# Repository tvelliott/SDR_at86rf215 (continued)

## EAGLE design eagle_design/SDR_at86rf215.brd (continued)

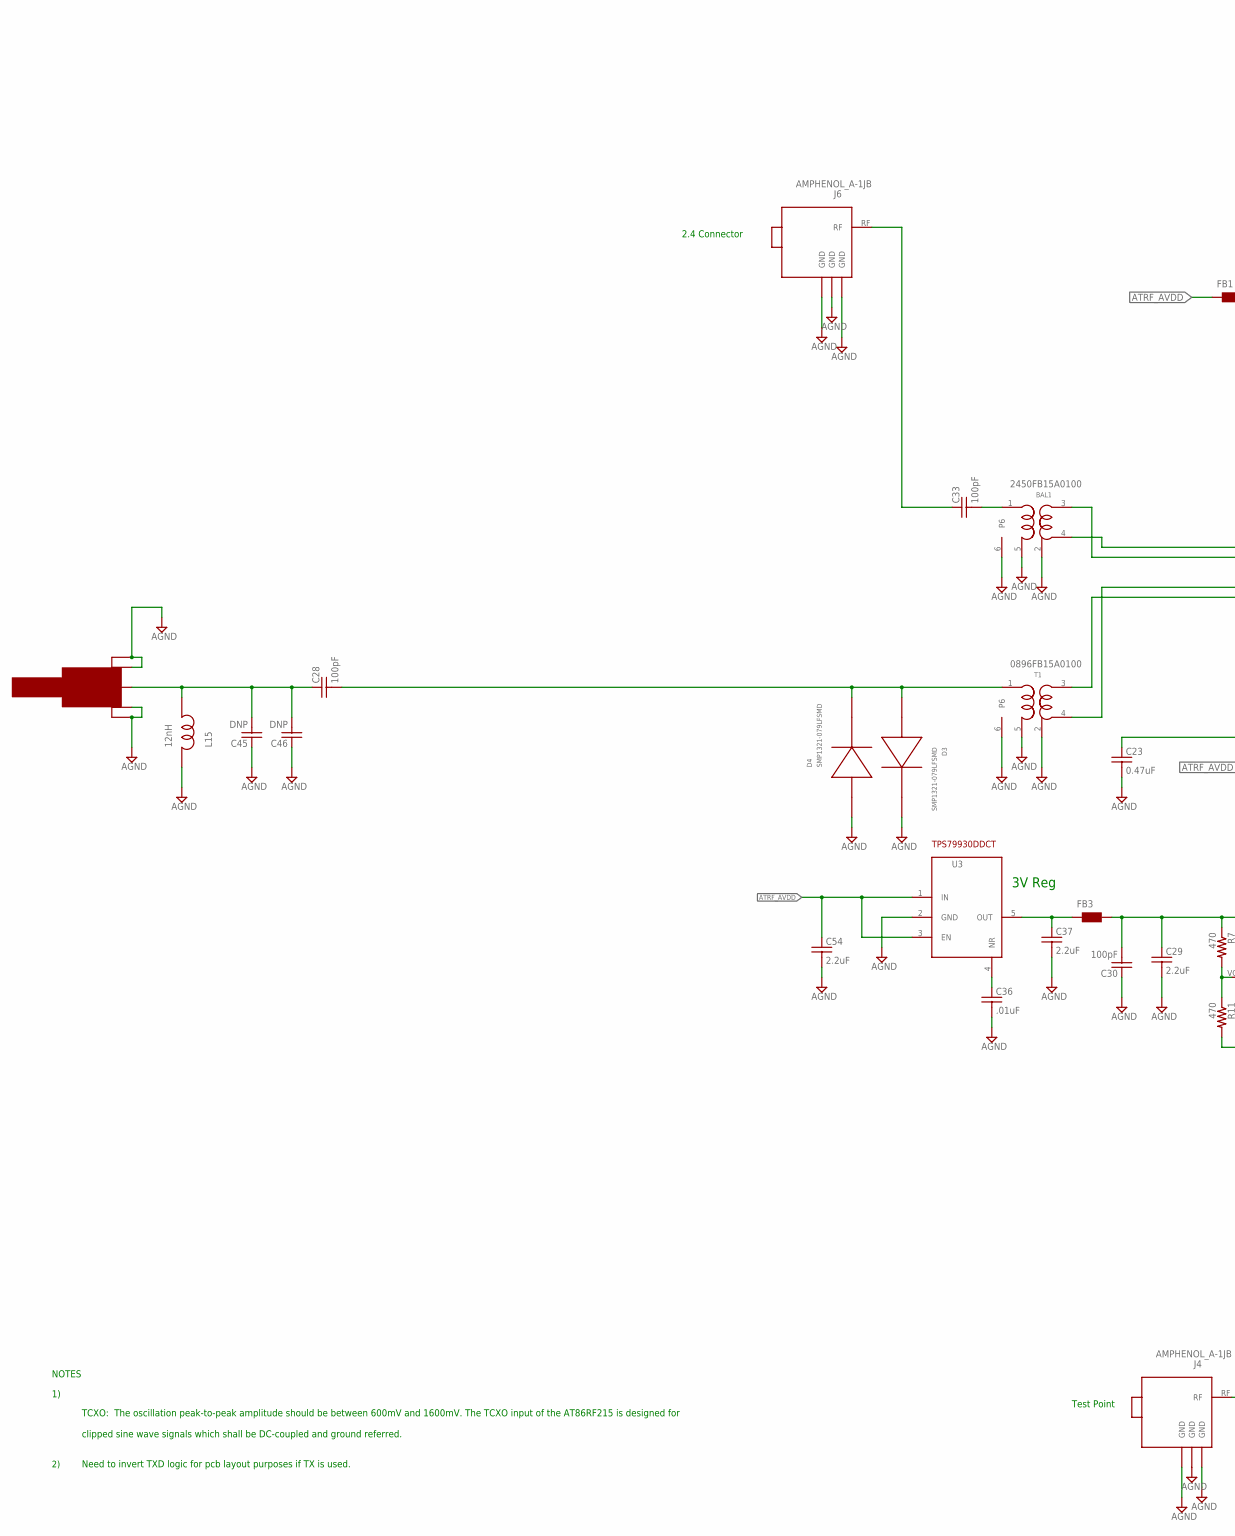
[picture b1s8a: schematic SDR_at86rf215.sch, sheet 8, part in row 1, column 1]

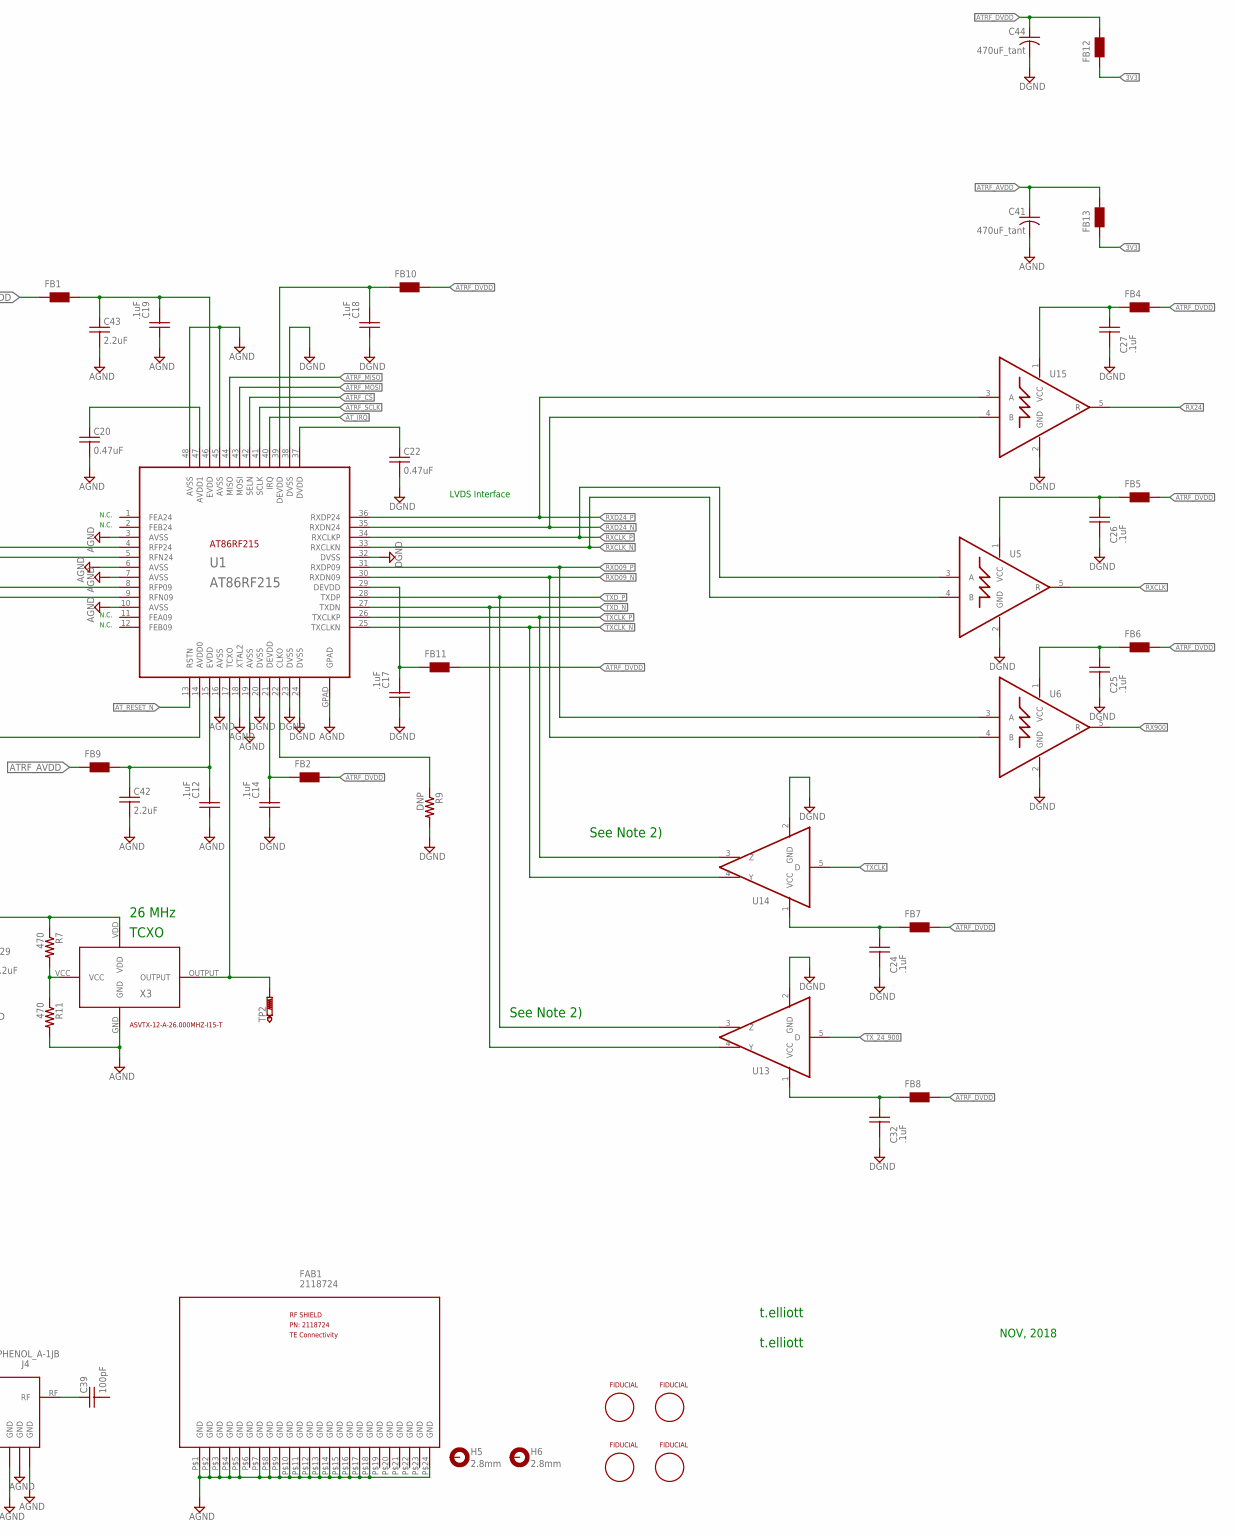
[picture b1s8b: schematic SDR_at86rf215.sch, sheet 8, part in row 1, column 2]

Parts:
BAL1: 2450FB15A0100; BALUN
C12, C14, C17, C18, C19, C24, C25, C26, C27, C32: .1uF; C0402
C20, C22, C23: 0.47uF; C0603
C28, C30, C33, C39: 100pF; C0603
C29, C37, C42, C43, C54: 2.2uF; C0603
C36: .01uF; C0603
C41, C44: 470uF_tant; 1210K
C45, C46: DNP; C0603
D3, D4: SMP1321-079LFSMD; SC-79_PINDIODE
FAB1: 2118724; RF_SHIELD
FB1, FB2, FB3, FB4, FB5, FB6, FB7, FB8, FB9, FB10, FB11, FB12, FB13: WE-CBF_0603; 0603
FID5, FID6, FID7, FID8: FIDUCIALSMD; FIDUCIAL
H5, H6: 2.8mm; 2,8-PAD
J3: SMA0.062; SMA_EDGE
J4, J6: AMPHENOL_A-1JB; UFLCONNECTOR
L15: 12nH; C0603
R7, R11: 470; R0603_COMPACT
R9: DNP; R0603_COMPACT
T1: 0896FB15A0100; BALUN
TP2: PTR1TP08R; TP08R
U1: AT86RF215; QFN48
U3: TPS799X; SOT23-6
U5, U6, U15: SN65LVDT2; SOT23-5
U13, U14: SN65LVDS1; SOT23-5
X3: ASVTX-12-A-40.000MHZ-H10-T; CRYSTAL_2.5_2MM

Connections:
3V: C29.1, C30.2, FB3.2, R7.1, X3.VDD
3V3: FB12.1, FB13.1; also elsewhere on the board
ATRF_AVDD: C41.A, C54.1, FB1.1, FB9.1, FB13.2, U3.1 (IN), U3.3 (EN)
ATRF_CS: U1.42 (SELN); also elsewhere on the board
ATRF_DVDD: C44.A, FB2.2, FB4.2, FB5.2, FB6.2, FB7.2, FB8.2, FB10.2, FB11.2, FB12.2
ATRF_MISO: U1.44 (MISO); also elsewhere on the board
ATRF_MOSI: U1.43 (MOSI); also elsewhere on the board
ATRF_SCLK: U1.41 (SCLK); also elsewhere on the board
AT_IRQ: U1.40 (IRQ); also elsewhere on the board
AT_RESET_N: U1.13 (RSTN); also elsewhere on the board
GND: BAL1.2 (FEED), BAL1.5 (GND), BAL1.6, C12.1, C14.1, C17.1, C18.1, C19.1, C20.2, C22.2, C23.2, C24.2, C25.2, C26.2, C27.2, C29.2, C30.1, C32.2, C36.2, C37.2, C41.C, C42.2, C43.2, C44.C, C45.1, C46.1, C54.2, D3.C, D4.A, FAB1.P$1, FAB1.P$2, FAB1.P$3, FAB1.P$4, FAB1.P$5, FAB1.P$7, FAB1.P$8, FAB1.P$9, FAB1.P$10, FAB1.P$11, FAB1.P$12, FAB1.P$13, FAB1.P$14, FAB1.P$15, FAB1.P$16, FAB1.P$17, FAB1.P$18, FAB1.P$24, J3.GND1, J3.GND2 (GND3), J3.GND3 (GND2), J3.GND4, J4.1 (GND), J4.2 (GND), J4.3 (GND), J6.1 (GND), J6.2 (GND), J6.3 (GND), L15.2, R9.2, R11.2, T1.2 (FEED), T1.5 (GND), T1.6, U1.3 (AVSS), U1.6 (AVSS), U1.7 (AVSS), U1.10 (AVSS), U1.16 (AVSS), U1.18 (XTAL2), U1.19 (AVSS), U1.20 (DVSS), U1.23 (DVSS), U1.24 (DVSS), U1.32 (DVSS), U1.38 (DVSS), U1.45 (AVSS), U1.48 (AVSS), U1.GPAD, U3.2 (GND), U5.2 (GND), U6.2 (GND), U13.2 (GND), U14.2 (GND), U15.2 (GND), X3.GND; also elsewhere on the board
unnamed: C36.1, U3.4 (NR)
unnamed: TP2.TP, U1.17 (TCXO), X3.OUTPUT
unnamed: C26.1, FB5.1, U5.1 (VCC)
unnamed: C20.1, U1.47 (AVDD1)
unnamed: C22.1, U1.37 (DVDD)
unnamed: C28.1, C45.2, C46.2, J3.RF, L15.1
unnamed: R7.2, R11.1, X3.VCC
unnamed: C27.1, FB4.1, U15.1 (VCC)
unnamed: C23.1, U1.14 (AVDD0)
unnamed: C39.1, J4.RF
unnamed: C32.1, FB8.1, U13.1 (VCC)
unnamed: R9.1, U1.22 (CLKO)
unnamed: BAL1.1 (UBAL), C33.2
unnamed: C12.2, C42.1, FB9.2, U1.15 (EVDD)
unnamed: C33.1, J6.RF
unnamed: C24.1, FB7.1, U14.1 (VCC)
unnamed: C25.1, FB6.1, U6.1 (VCC)
unnamed: C19.2, C43.1, FB1.2, U1.46 (EVDD)
unnamed: C14.2, FB2.1, U1.21 (DEVDD)
unnamed: C18.2, FB10.1, U1.39 (DEVDD)
unnamed: C17.2, FB11.1, U1.29 (DEVDD)
unnamed: C28.2, D3.A, D4.C, T1.1 (UBAL)
unnamed: C37.1, FB3.1, U3.5 (OUT)
RF09_N: T1.3 (BP2), U1.9 (RFN09)
RF09_P: T1.4 (BP1), U1.8 (RFP09)
RF24_N: BAL1.3 (BP2), U1.5 (RFN24)
RF24_P: BAL1.4 (BP1), U1.4 (RFP24)
RX24: U15.5 (R); also elsewhere on the board
RX900: U6.5 (R); also elsewhere on the board
RXCLK: U5.5 (R); also elsewhere on the board
RXCLK_N: U1.33 (RXCLKN), U5.4 (B)
RXCLK_P: U1.34 (RXCLKP), U5.3 (A)
RXD09_N: U1.30 (RXDN09), U6.4 (B)
RXD09_P: U1.31 (RXDP09), U6.3 (A)
RXD24_N: U1.35 (RXDN24), U15.4 (B)
RXD24_P: U1.36 (RXDP24), U15.3 (A)
TXCLK: U14.5 (D); also elsewhere on the board
TXCLK_N: U1.25 (TXCLKN), U14.4 (Y)
TXCLK_P: U1.26 (TXCLKP), U14.3 (Z)
TXD_N: U1.27 (TXDN), U13.4 (Y)
TXD_P: U1.28 (TXDP), U13.3 (Z)
TX_24_900: U13.5 (D); also elsewhere on the board

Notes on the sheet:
t.elliott
TCXO: The oscillation peak-to-peak amplitude should be between 600mV and 1600mV. The TCXO input of the AT86RF215 is designed for clipped sine wave signals which shall be DC-coupled and ground referred.
NOTES
TCXO
26 MHz
3V Reg
ASVTX-12-A-26.000MHZ-I15-T
LVDS Interface
See Note 2)
Need to invert TXD logic for pcb layout purposes if TX is used.
2.4 Connector
Test Point
N.C.
NOV, 2018

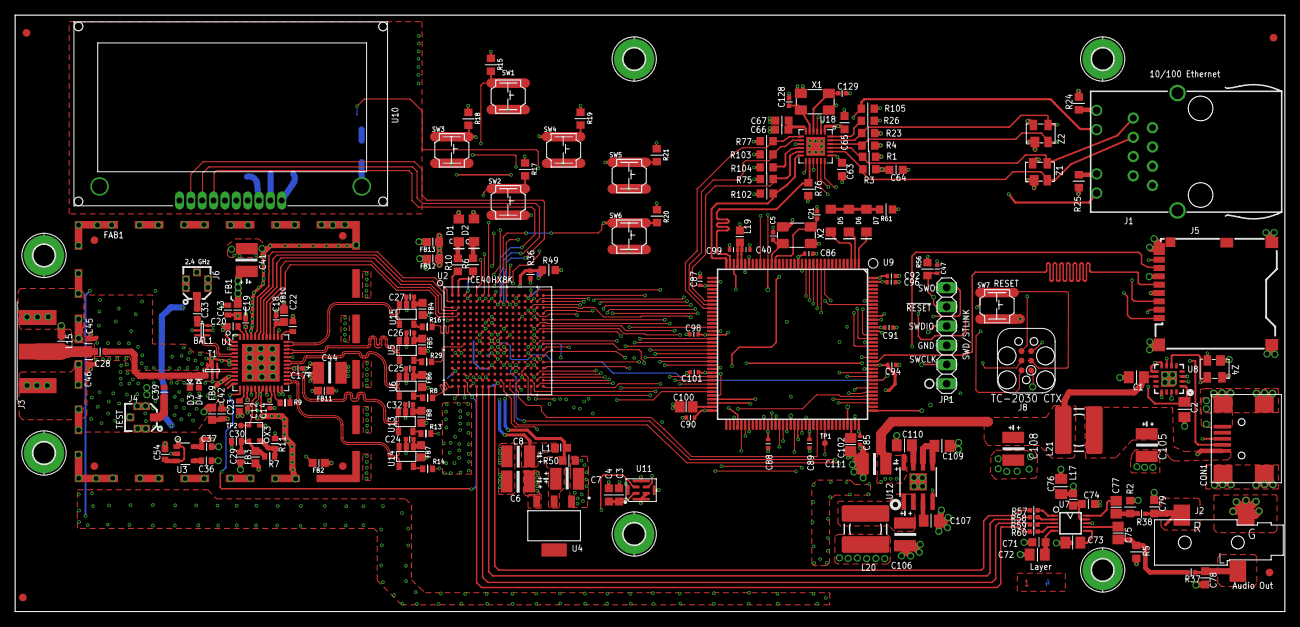
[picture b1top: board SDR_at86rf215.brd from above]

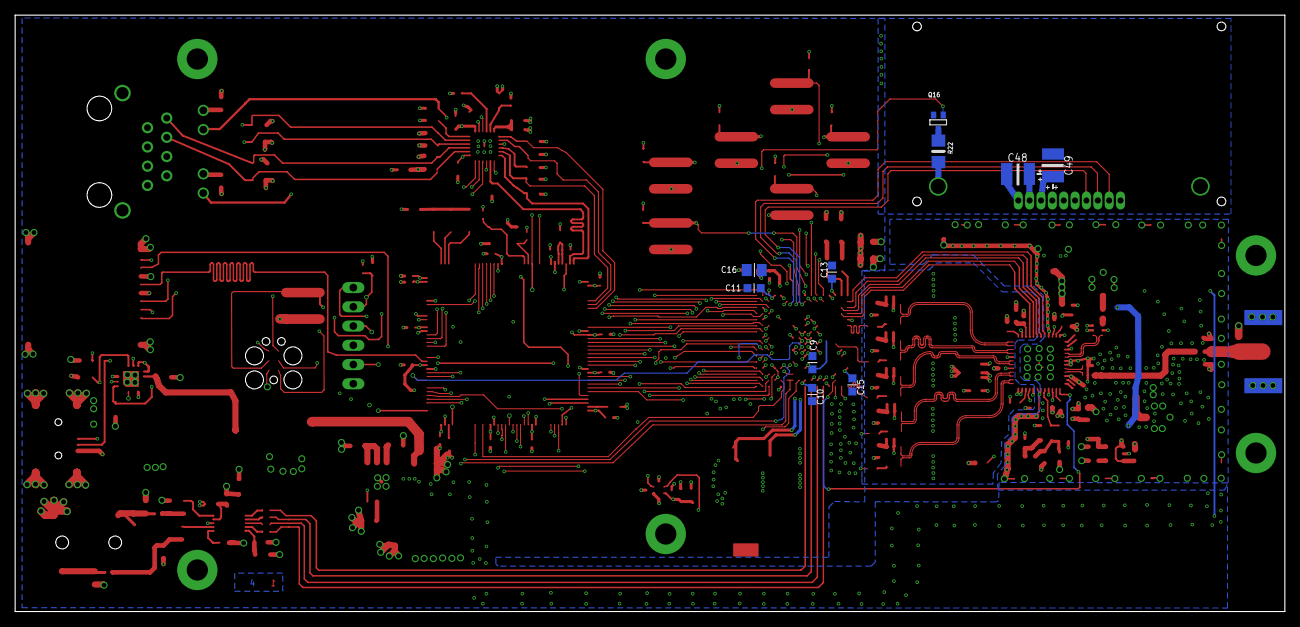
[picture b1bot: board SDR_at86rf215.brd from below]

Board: 4 copper layers, 167.6 x 78.7 mm, 212 parts (10 on the bottom side), 198 nets.

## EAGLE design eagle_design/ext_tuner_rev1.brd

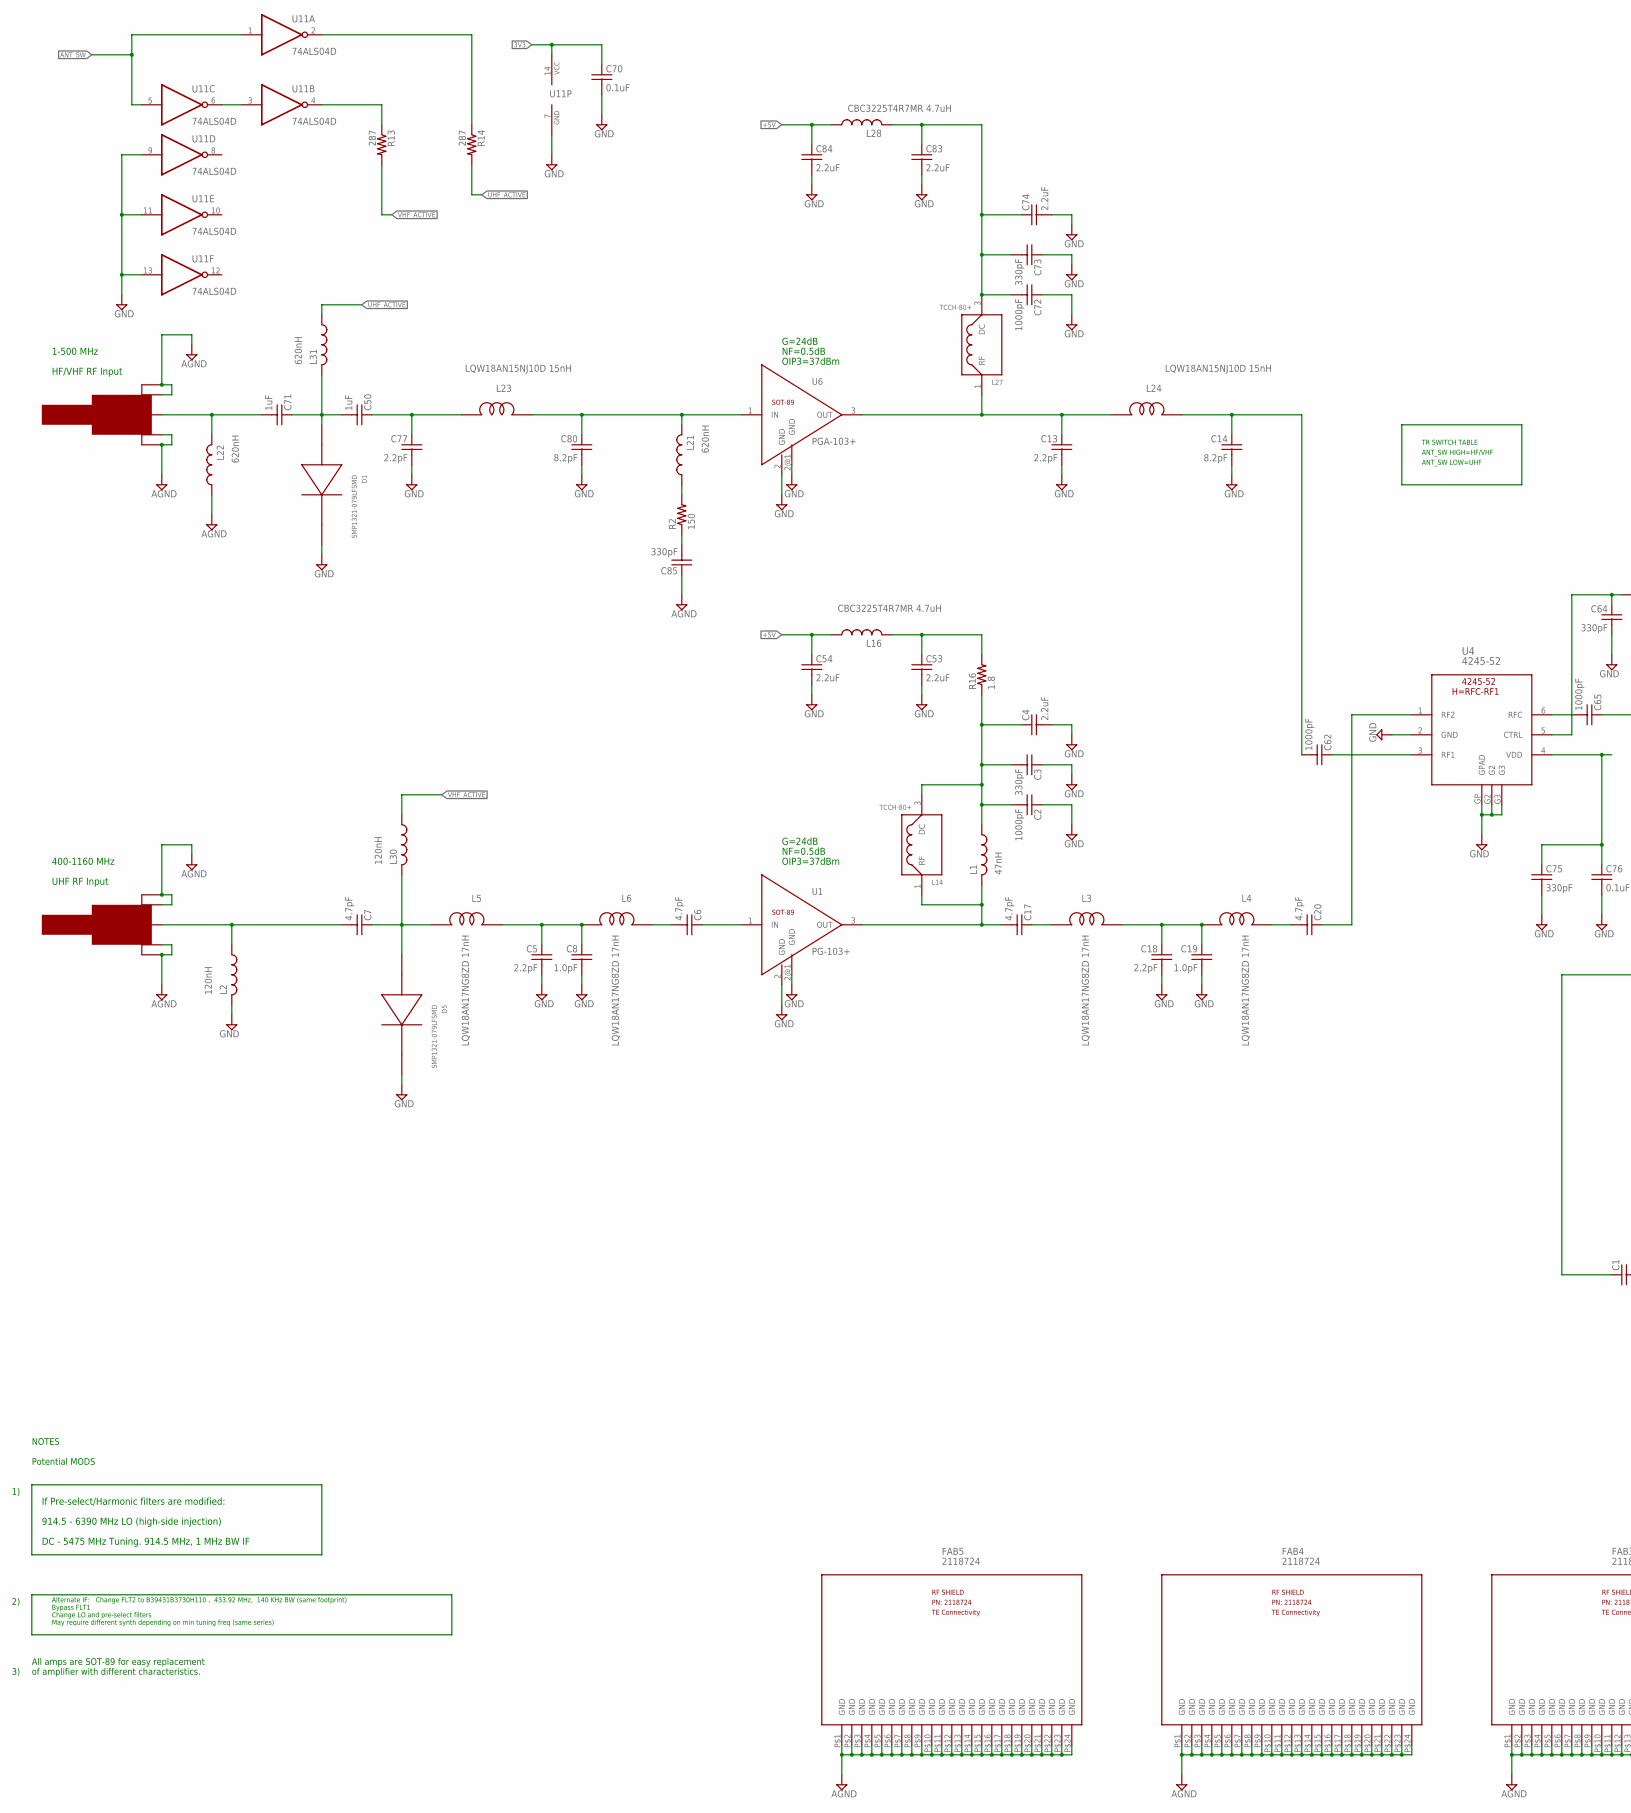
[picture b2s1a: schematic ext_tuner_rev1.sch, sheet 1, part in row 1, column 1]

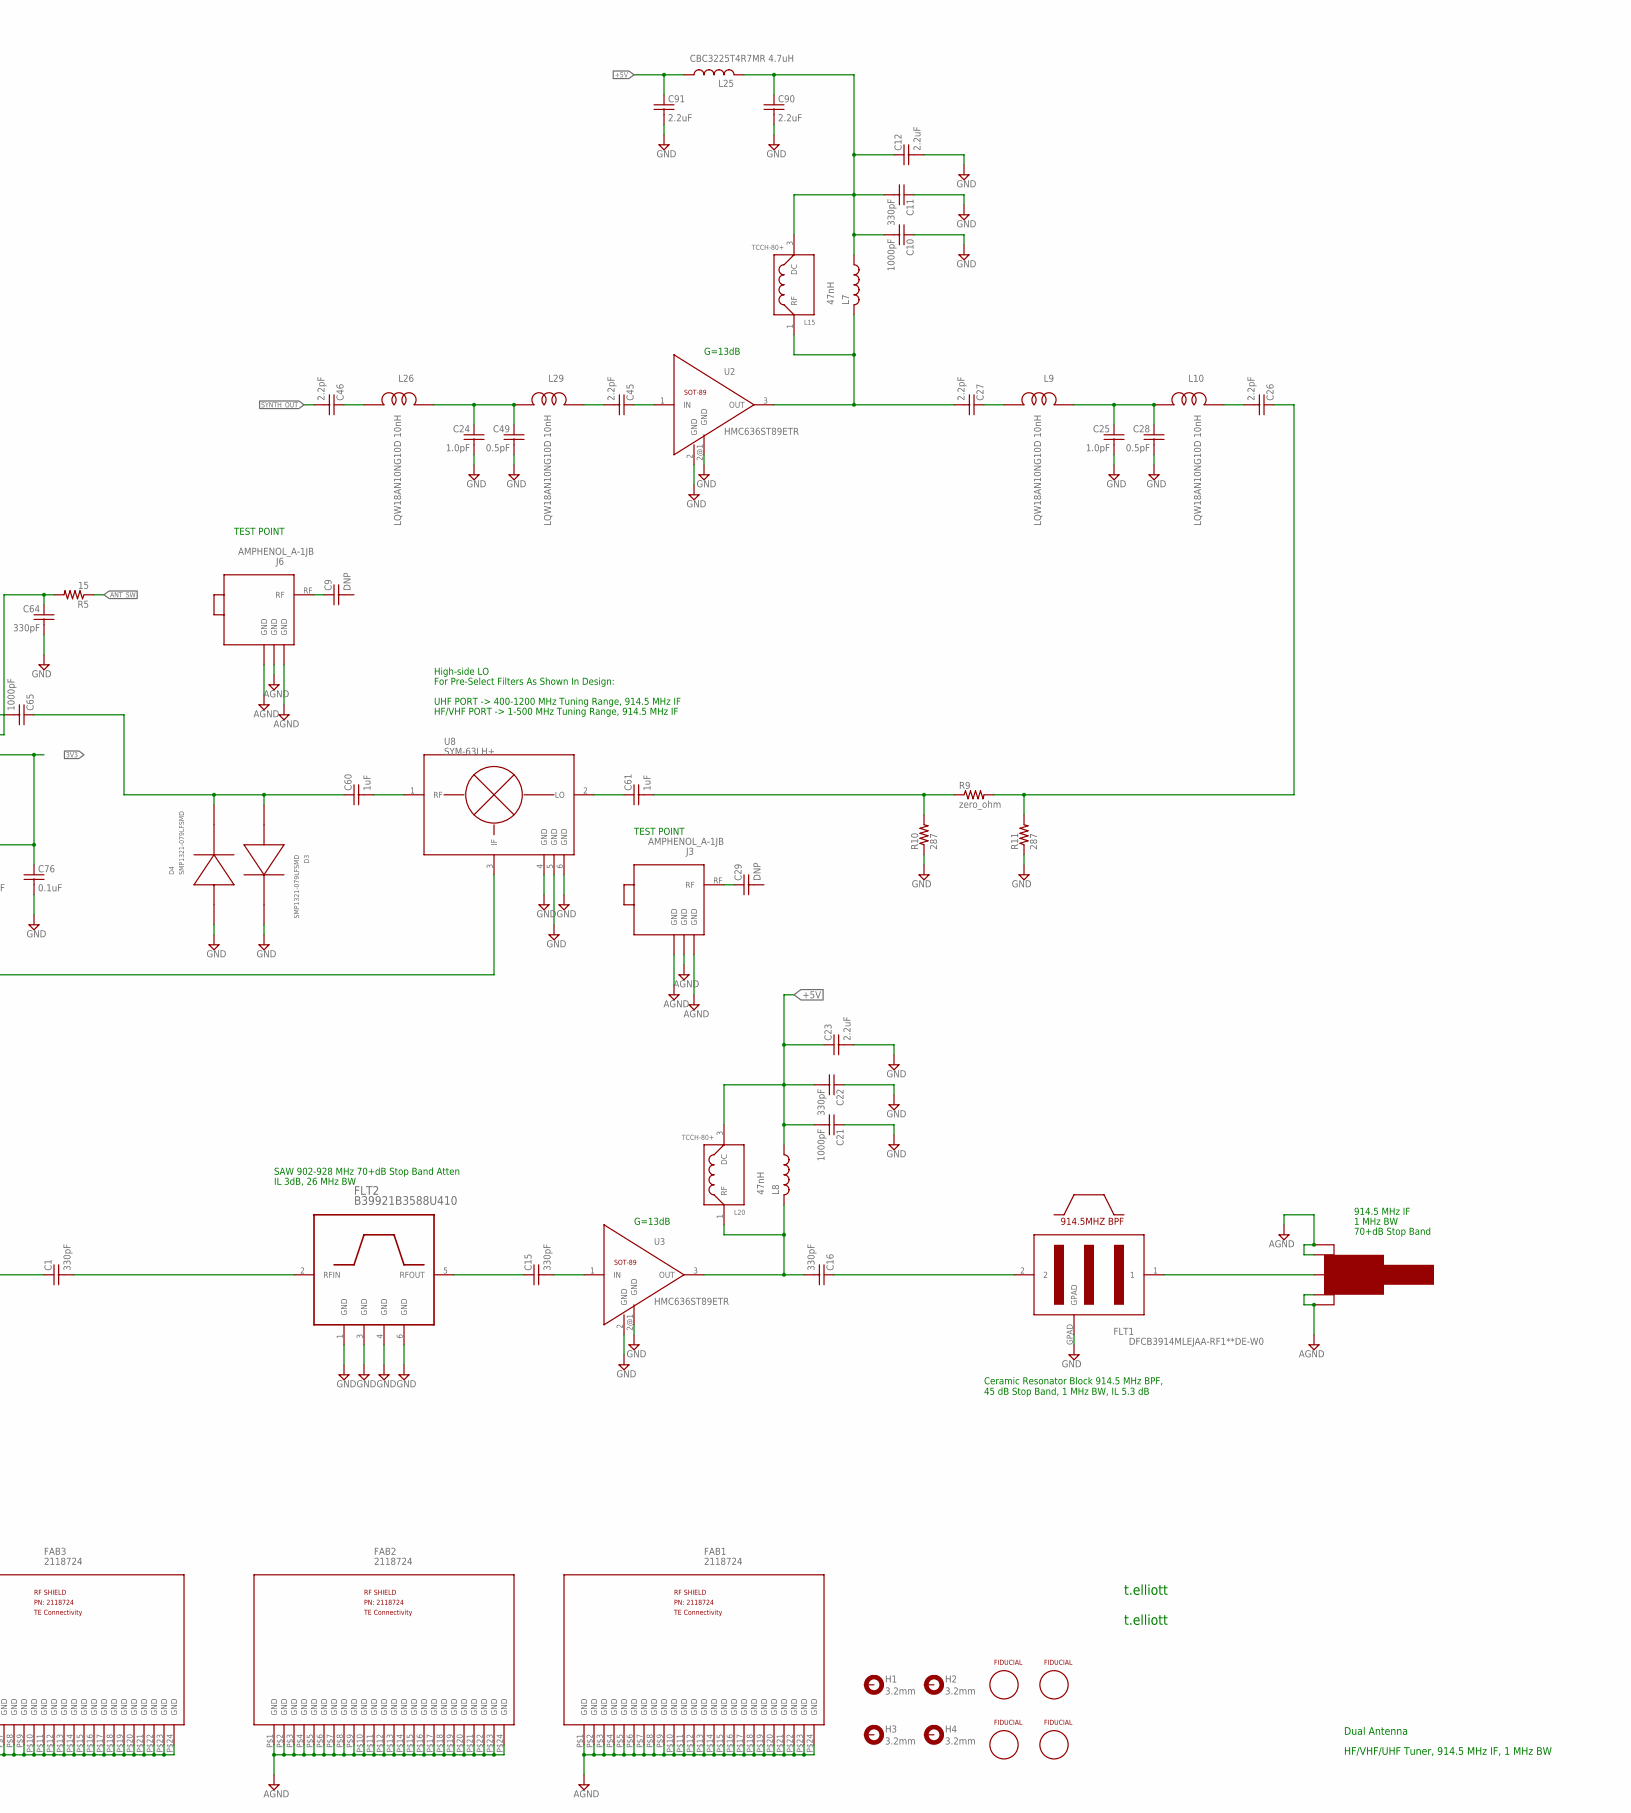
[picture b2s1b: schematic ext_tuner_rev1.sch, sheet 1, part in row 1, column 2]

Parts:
C1, C3, C11, C15, C16, C22, C64, C73, C75, C85: 330pF; C0603
C2, C10, C21, C62, C65, C72: 1000pF; C0603
C4, C12, C23, C53, C54, C74, C83, C84, C90, C91: 2.2uF; C0603
C5, C13, C18, C26, C27, C45, C46, C77: 2.2pF; C0603
C6, C7, C17, C20: 4.7pF; C0603
C8, C19, C24, C25: 1.0pF; C0603
C9, C29: DNP; C0603
C14, C80: 8.2pF; C0603
C28, C49: 0.5pF; C0603
C50, C60, C61, C71: 1uF; C0603
C70, C76: 0.1uF; C0402@1
D1, D3, D4, D5: SMP1321-079LFSMD; SC-79_PINDIODE
FAB1, FAB2, FAB3, FAB4, FAB5: 2118724; RF_SHIELD
FID1, FID2, FID3, FID4: FIDUCIALSMD; FIDUCIAL
FLT1: DFCB3914MLEJAA-RF1**DE-W0; SAWMURATA914
FLT2: B39921B3588U410; SM3030-6
H1, H2, H3, H4: 3.2mm; 2,8-PAD
J1, J2, J4: SMA0.062; SMA_EDGE
J3, J6: AMPHENOL_A-1JB; UFLCONNECTOR
L1, L7, L8: 47nH; L3225M; PARTNUMBER ELJ-PA331KF
L2, L30: 120nH; L3225M; PARTNUMBER ELJ-PA331KF
L3, L4, L5, L6: LQW18AN17NG8ZD 17nH; MURATA_LQW_0603
L9, L10, L26, L29: LQW18AN10NG10D 10nH; MURATA_LQW_0603
L14, L15, L20, L27: TCCH-80+
L16, L25, L28: CBC3225T4R7MR 4.7uH; L3225M; PARTNUMBER ELJ-PA331KF
L21, L22, L31: 620nH; L3225M; PARTNUMBER ELJ-PA331KF
L23, L24: LQW18AN15NJ10D 15nH; MURATA_LQW_0603
R2: 150; R1206
R5: 15; 0402$1
R9: zero_ohm; R0603
R10, R11: 287; R0603
R13, R14: 287; 0603
R16: 1.8; R1206
U1: PG-103+; SOT89
U2, U3: HMC636ST89ETR; SOT89
U4: 4245-52; PE4245
U6: PGA-103+; SOT89
U8: SYM-63LH+; SYM-18H
U11: 74ALS04D; SO14

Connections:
3V3: C70.1, C75.1, C76.1, U4.4 (VDD), U11.14 (VCC); also elsewhere on the board
+5V: C21.2, C22.2, C23.1, C54.1, C84.1, C91.1, L8.1, L16.1, L20.3 (DC), L25.1, L28.1; also elsewhere on the board
ANT_SW: R5.1, U11.1 (I), U11.5 (I); also elsewhere on the board
GND: C2.1, C3.1, C4.2, C5.2, C8.2, C10.1, C11.1, C12.2, C13.2, C14.2, C18.2, C19.2, C21.1, C22.1, C23.2, C24.2, C25.2, C28.2, C49.2, C53.2, C54.2, C64.2, C70.2, C72.1, C73.1, C74.2, C75.2, C76.2, C77.2, C80.2, C83.2, C84.2, C85.1, C90.2, C91.2, D1.C, D3.C, D4.A, D5.C, FAB1.P$1, FAB1.P$2, FAB1.P$3, FAB1.P$4, FAB1.P$5, FAB1.P$6, FAB1.P$7, FAB1.P$8, FAB1.P$9, FAB1.P$10, FAB1.P$11, FAB1.P$12, FAB1.P$13, FAB1.P$14, FAB1.P$15, FAB1.P$16, FAB1.P$17, FAB1.P$18, FAB1.P$19, FAB1.P$20, FAB1.P$21, FAB1.P$22, FAB1.P$23, FAB1.P$24, FAB2.P$1, FAB2.P$2, FAB2.P$3, FAB2.P$4, FAB2.P$5, FAB2.P$6, FAB2.P$7, FAB2.P$8, FAB2.P$9, FAB2.P$10, FAB2.P$11, FAB2.P$12, FAB2.P$13, FAB2.P$14, FAB2.P$15, FAB2.P$16, FAB2.P$17, FAB2.P$18, FAB2.P$19, FAB2.P$20, FAB2.P$21, FAB2.P$22, FAB2.P$23, FAB2.P$24, FAB3.P$1, FAB3.P$2, FAB3.P$3, FAB3.P$4, FAB3.P$5, FAB3.P$6, FAB3.P$7, FAB3.P$8, FAB3.P$9, FAB3.P$10, FAB3.P$11, FAB3.P$12, FAB3.P$13, FAB3.P$14, FAB3.P$15, FAB3.P$16, FAB3.P$17, FAB3.P$18, FAB3.P$19, FAB3.P$20, FAB3.P$21, FAB3.P$22, FAB3.P$23, FAB3.P$24, FAB4.P$1, FAB4.P$2, FAB4.P$3, FAB4.P$4, FAB4.P$5, FAB4.P$6, FAB4.P$7, FAB4.P$8, FAB4.P$9, FAB4.P$10, FAB4.P$11, FAB4.P$12, FAB4.P$13, FAB4.P$14, FAB4.P$15, FAB4.P$16, FAB4.P$17, FAB4.P$18, FAB4.P$19, FAB4.P$20, FAB4.P$21, FAB4.P$22, FAB4.P$23, FAB4.P$24, FAB5.P$1, FAB5.P$2, FAB5.P$3, FAB5.P$4, FAB5.P$5, FAB5.P$6, FAB5.P$7, FAB5.P$8, FAB5.P$9, FAB5.P$10, FAB5.P$11, FAB5.P$12, FAB5.P$13, FAB5.P$14, FAB5.P$15, FAB5.P$16, FAB5.P$17, FAB5.P$18, FAB5.P$19, FAB5.P$20, FAB5.P$21, FAB5.P$22, FAB5.P$23, FAB5.P$24, FLT1.GPAD, FLT2.1 (GND), FLT2.3 (GND), FLT2.4 (GND), FLT2.6 (GND), J1.GND1, J1.GND2 (GND3), J1.GND3 (GND2), J1.GND4, J2.GND1, J2.GND2 (GND3), J2.GND3 (GND2), J2.GND4, J3.1 (GND), J3.2 (GND), J3.3 (GND), J4.GND1, J4.GND2 (GND3), J4.GND3 (GND2), J4.GND4, J6.1 (GND), J6.2 (GND), J6.3 (GND), L2.2, L22.1, R10.1, R11.1, U1.2 (GND), U1.2@1 (GND), U2.2 (GND), U2.2@1 (GND), U3.2 (GND), U3.2@1 (GND), U4.2 (GND), U4.G2, U4.G3, U4.GP (GPAD), U6.2 (GND), U6.2@1 (GND), U8.4 (GND), U8.5 (GND), U8.6 (GND), U11.7 (GND), U11.9 (I), U11.11 (I), U11.13 (I); also elsewhere on the board
unnamed: C15.2, U3.1 (IN)
unnamed: C17.2, L1.2, L14.1 (RF), U1.3 (OUT)
unnamed: C1.2, FLT2.2 (RFIN)
unnamed: C62.1, U4.3 (RF1)
unnamed: C16.1, FLT1.2
unnamed: C6.1, U1.1 (IN)
unnamed: C9.1, J6.RF
unnamed: C7.1, D5.A, L5.1, L30.2
unnamed: C46.1, L26.1
unnamed: C5.1, C8.1, L5.2, L6.1
unnamed: C6.2, L6.2
unnamed: C1.1, U8.3 (IF)
unnamed: C60.1, C65.1, D3.A, D4.C
unnamed: C61.2, R9.1, R10.2
unnamed: C26.1, R9.2, R11.2
unnamed: C17.1, L3.1
unnamed: C27.2, L7.2, L15.1 (RF), U2.3 (OUT)
unnamed: C16.2, L8.2, L20.1 (RF), U3.3 (OUT)
unnamed: C20.1, U4.1 (RF2)
unnamed: C18.1, C19.1, L3.2, L4.1
unnamed: C20.2, L4.2
unnamed: C64.1, R5.2, U4.5 (CTRL)
unnamed: C15.1, FLT2.5 (RFOUT)
unnamed: FLT1.1, J2.RF
unnamed: C27.1, L9.1
unnamed: C25.1, C28.1, L9.2, L10.1
unnamed: C26.2, L10.2
unnamed: C50.2, C71.1, D1.A, L31.2
unnamed: C85.2, R2.1
unnamed: C29.1, J3.RF
unnamed: C53.1, L16.2, R16.2
unnamed: C72.2, C73.2, C74.1, C83.1, L27.3 (DC), L28.2
unnamed: C61.1, U8.2 (LO)
unnamed: C65.2, U4.6 (RFC)
unnamed: C13.1, L24.1, L27.1 (RF), U6.3 (OUT)
unnamed: L21.1, R2.2
unnamed: C80.1, L21.2, L23.2, U6.1 (IN)
unnamed: C71.2, J4.RF, L22.2
unnamed: C24.1, C49.1, L26.2, L29.1
unnamed: C14.1, C62.2, L24.2
unnamed: C60.2, U8.1 (RF)
unnamed: C45.2, L29.2
unnamed: C2.2, C3.2, C4.1, L1.1, L14.3 (DC), R16.1
unnamed: C45.1, U2.1 (IN)
unnamed: C50.1, C77.1, L23.1
unnamed: R13.1, U11.4 (O)
unnamed: R14.1, U11.2 (O)
unnamed: U11.3 (I), U11.6 (O)
unnamed: C10.2, C11.2, C12.1, C90.1, L7.1, L15.3 (DC), L25.2
SYNTH_OUT: C46.2; also elsewhere on the board
UHF_ACTIVE: L31.1, R14.2
UHF_IN: C7.2, J1.RF, L2.1
VHF_ACTIVE: L30.1, R13.2

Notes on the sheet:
t.elliott
914.5 - 6390 MHz LO (high-side injection)
DC - 5475 MHz Tuning. 914.5 MHz, 1 MHz BW IF
G=13dB
G=13dB
UHF PORT -> 400-1200 MHz Tuning Range, 914.5 MHz IF
If Pre-select/Harmonic filters are modified:
High-side LO
914.5 MHz IF
TEST POINT
1 MHz BW
70+dB Stop Band
For Pre-Select Filters As Shown In Design:
SAW 902-928 MHz 70+dB Stop Band Atten
Ceramic Resonator Block 914.5 MHz BPF, 45 dB Stop Band, 1 MHz BW, IL 5.3 dB
UHF RF Input
400-1160 MHz
IL 3dB, 26 MHz BW
HF/VHF RF Input
1-500 MHz
G=24dB
NF=0.5dB
HF/VHF/UHF Tuner, 914.5 MHz IF, 1 MHz BW
Dual Antenna
HF/VHF PORT -> 1-500 MHz Tuning Range, 914.5 MHz IF
Alternate IF: Change FLT2 to B39431B3730H110 , 433.92 MHz, 140 KHz BW (same footprint) Bypass FLT1 Change LO and pre-select filters May require different synth depending on min tuning freq (same series)
Potential MODS
NOTES
All amps are SOT-89 for easy replacement of amplifier with different characteristics.
OIP3=37dBm
ANT_SW HIGH=HF/VHF
ANT_SW LOW=UHF
TR SWITCH TABLE

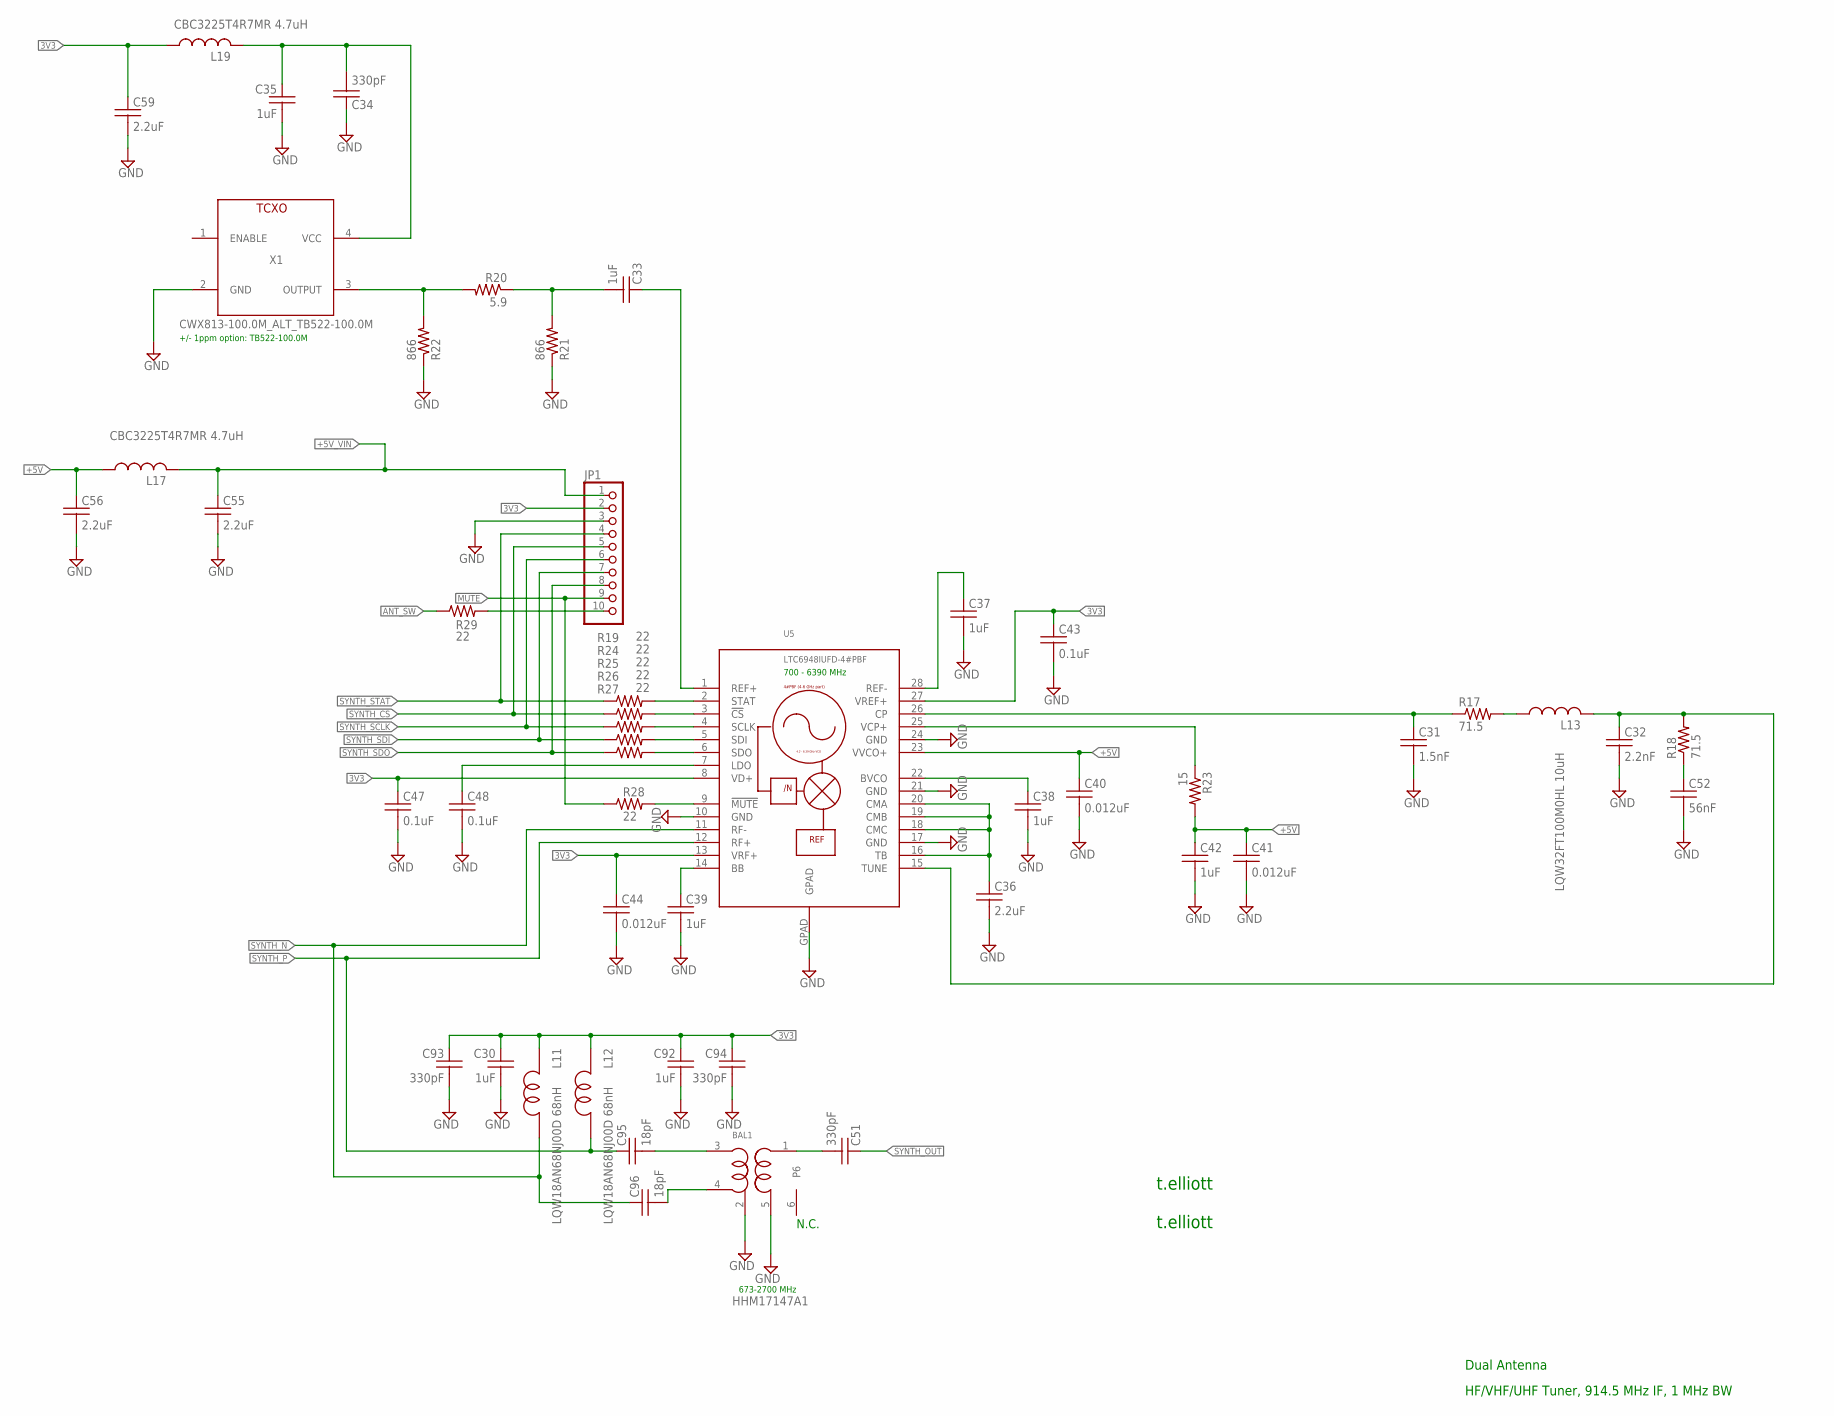
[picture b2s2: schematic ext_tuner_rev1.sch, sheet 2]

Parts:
BAL1: HHM17147A1; TDK_BALUN_5PIN
C30, C33, C35, C92: 1uF; C0603
C31: 1.5nF; C0402@1
C32: 2.2nF; C0402@1
C34, C51, C93, C94: 330pF; C0603
C36, C55, C56, C59: 2.2uF; C0603
C37, C38, C39, C42: 1uF; C0402@1
C40, C41, C44: 0.012uF; C0402@1
C43, C47, C48: 0.1uF; C0402@1
C52: 56nF; C0402@1
C95, C96: 18pF; C0402@1
JP1: PINHD-1X10; 1X10
L11, L12: LQW18AN68NJ00D 68nH; MURATA_LQW_0603
L13: LQW32FT100M0HL 10uH; L3225M; PARTNUMBER ELJ-PA331KF
L17, L19: CBC3225T4R7MR 4.7uH; L3225M; PARTNUMBER ELJ-PA331KF
R17, R18: 71.5; R0402
R19, R24, R25, R26, R27, R28, R29: 22; R0603_COMPACT
R20: 5.9; R0603
R21, R22: 866; R0603
R23: 15; R0402
U5: LTC6948IUFD-4#PBF; QFN28_NONSQ
X1: CWX813-100.0M_ALT_TB522-100.0M; CWX8XX_5MM_7MM

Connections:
3V3: C30.1, C43.1, C44.1, C47.1, C59.1, C92.1, C93.1, C94.1, JP1.2, L11.2, L12.2, L19.1, U5.8 (VD+), U5.13 (VRF+), U5.27 (VREF+); also elsewhere on the board
!MUTE: JP1.9, R28.1; also elsewhere on the board
+5V: C40.1, C41.1, C42.1, C56.1, L17.1, R23.2, U5.23 (VVCO+); also elsewhere on the board
+5V_VIN: C55.1, JP1.1, L17.2; also elsewhere on the board
ANT_SW: R29.1; also elsewhere on the board
BALUN_N: BAL1.4 (BP1), C96.2
BALUN_P: BAL1.3 (BP2), C95.2
GND: BAL1.2 (FEED), BAL1.5 (GND), C30.2, C31.2, C32.2, C34.1, C35.2, C36.2, C37.2, C38.2, C39.2, C40.2, C41.2, C42.2, C43.2, C44.2, C47.2, C48.2, C52.2, C55.2, C56.2, C59.2, C92.2, C93.2, C94.2, JP1.3, R21.1, R22.1, U5.10 (GND), U5.17 (GND), U5.21 (GND), U5.24 (GND), U5.GPAD, X1.2 (GND); also elsewhere on the board
unnamed: R19.2, U5.2 (STAT)
unnamed: C52.1, R18.1
unnamed: C32.1, L13.2, R18.2, U5.15 (TUNE)
unnamed: L13.1, R17.2
unnamed: R24.2, U5.3 (!CS)
unnamed: R25.2, U5.4 (SCLK)
unnamed: R26.2, U5.5 (SDI)
unnamed: R27.2, U5.6 (SDO)
unnamed: C36.1, U5.16 (TB), U5.18 (CMC), U5.19 (CMB), U5.20 (CMA)
unnamed: R20.2, R22.2, X1.3 (OUTPUT)
unnamed: C33.1, U5.1 (REF+)
unnamed: C33.2, R20.1, R21.2
unnamed: C37.1, U5.28 (REF-)
unnamed: C38.1, U5.22 (BVCO)
unnamed: C39.1, U5.14 (BB)
unnamed: R23.1, U5.25 (VCP+)
unnamed: C48.1, U5.7 (LDO)
unnamed: R28.2, U5.9 (!MUTE)
unnamed: C31.1, R17.1, U5.26 (CP)
unnamed: BAL1.1 (UBAL), C51.2
unnamed: JP1.10, R29.2
unnamed: C34.2, C35.1, L19.2, X1.4 (VCC)
SYNTH_CS: JP1.5, R24.1; also elsewhere on the board
SYNTH_N: C96.1, L11.1, U5.11 (RF-)
SYNTH_OUT: C51.1; also elsewhere on the board
SYNTH_P: C95.1, L12.1, U5.12 (RF+)
SYNTH_SCLK: JP1.6, R25.1; also elsewhere on the board
SYNTH_SDI: JP1.7, R26.1; also elsewhere on the board
SYNTH_SDO: JP1.8, R27.1; also elsewhere on the board
SYNTH_STAT: JP1.4, R19.1; also elsewhere on the board

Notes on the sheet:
t.elliott
673-2700 MHz
700 - 6390 MHz
N.C.
+/- 1ppm option: TB522-100.0M
Dual Antenna
HF/VHF/UHF Tuner, 914.5 MHz IF, 1 MHz BW
